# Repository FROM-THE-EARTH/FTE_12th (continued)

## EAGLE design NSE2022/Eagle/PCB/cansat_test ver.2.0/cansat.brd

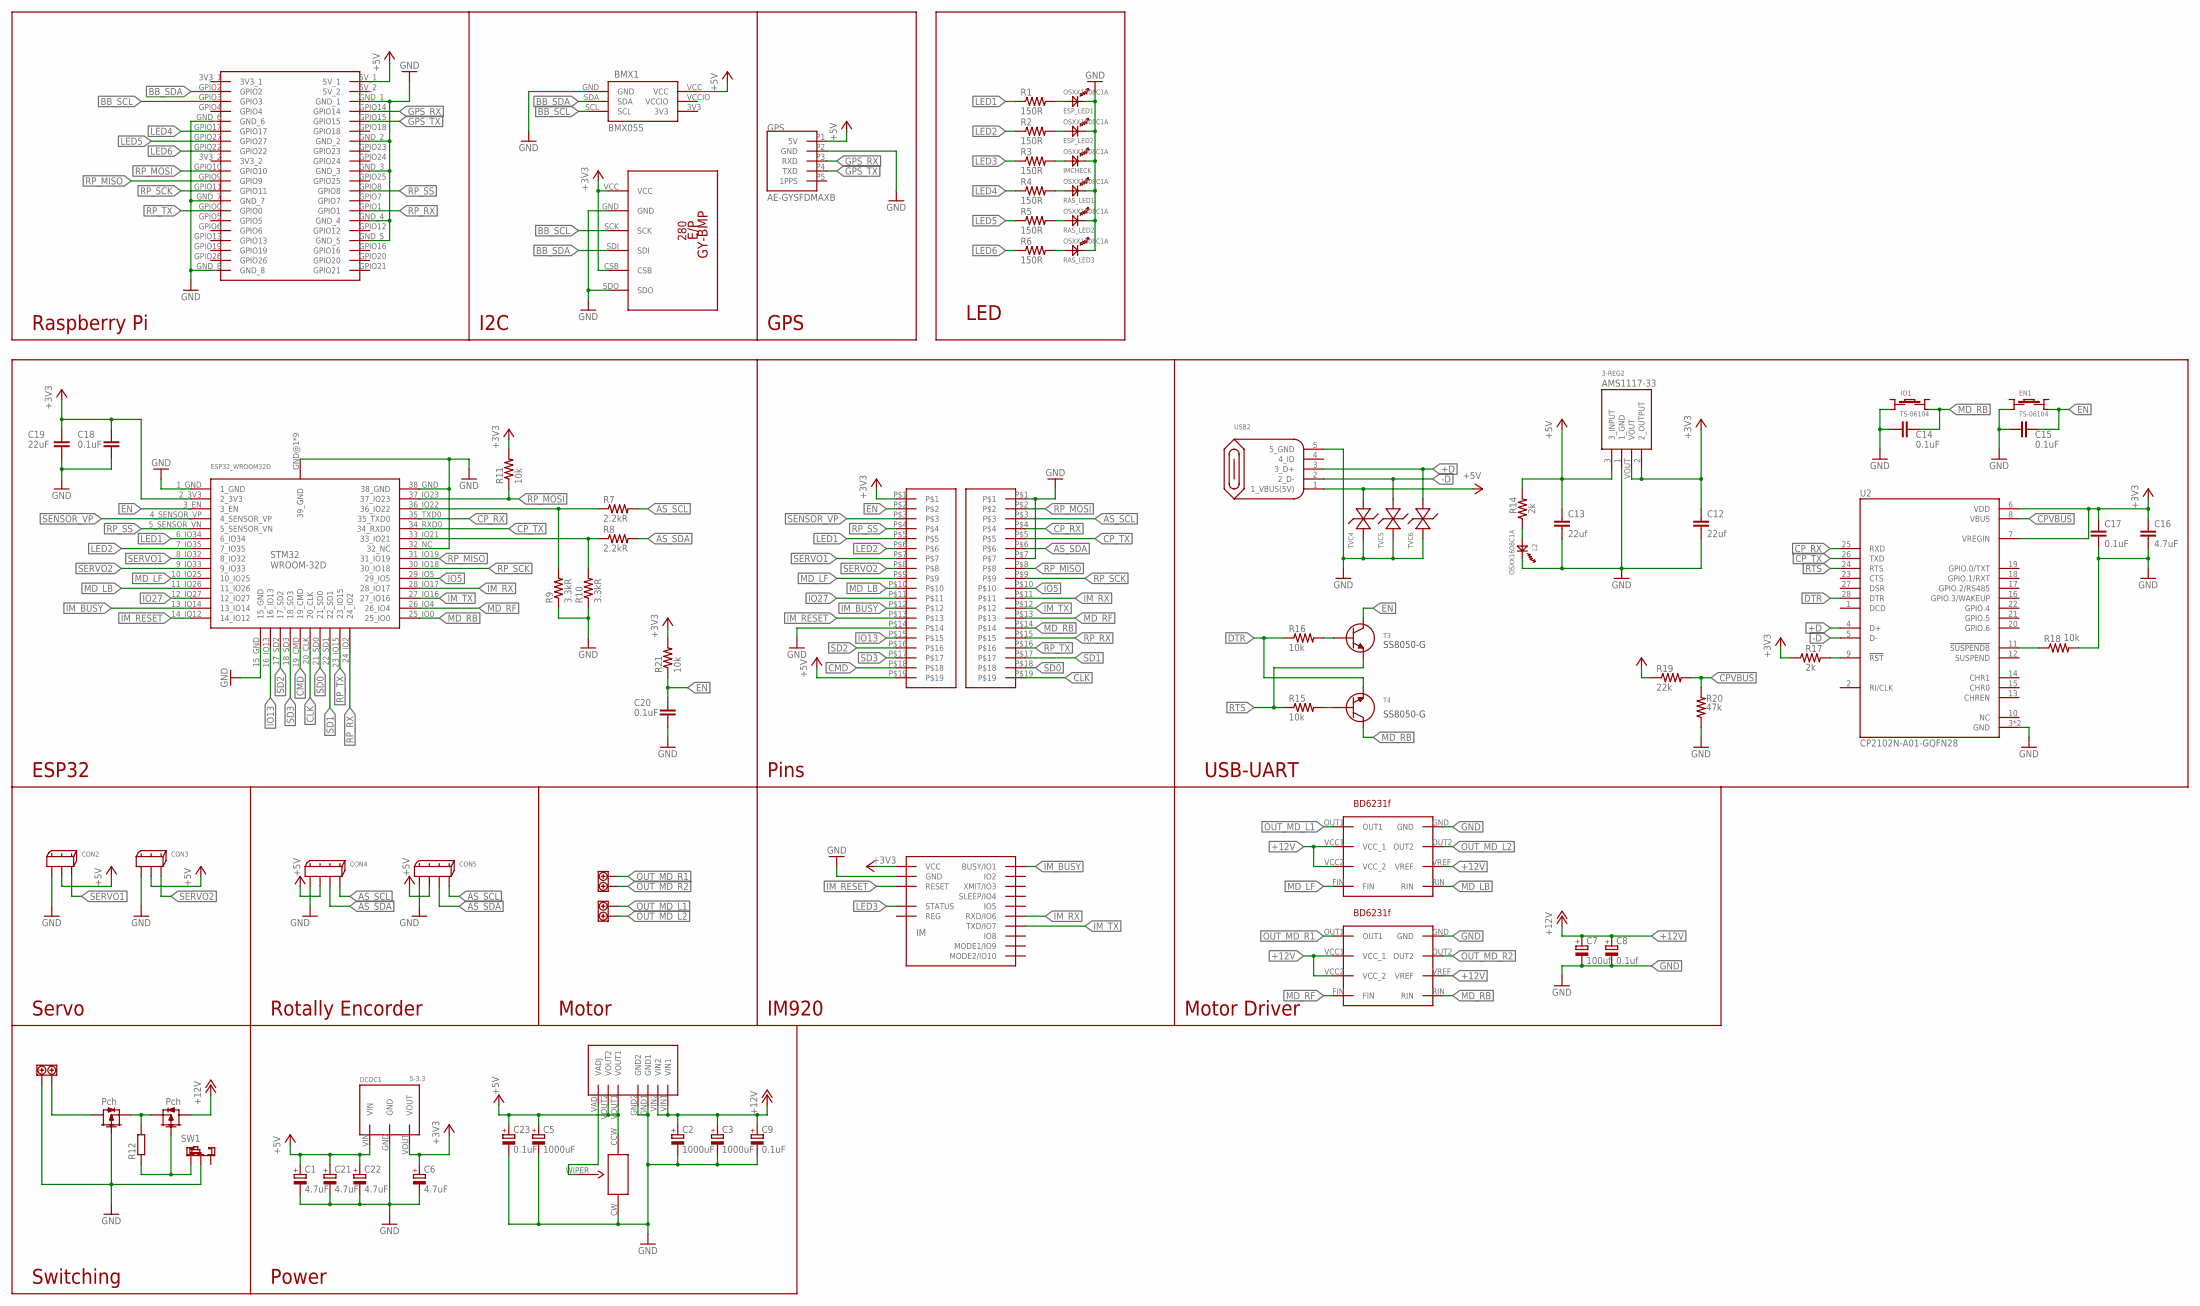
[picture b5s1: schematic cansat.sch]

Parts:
3-REG2: AZ1117CH-3.3TRG1
100KR1: 100kR; 3362P
BMX1: BMX055
C1, C6, C21, C22: 4.7uF; E2,5-7
C2, C3, C5: 1000uF; E5-10,5
C7: 100uf; E2,5-7
C8: 0.1uf; E2,5-7
C9: 0.1uF; E2,5-7
C12, C13: 22uf; C0603
C14, C15, C17, C18, C20: 0.1uF; C0603
C16: 4.7uF; C0402
C19: 22uF; C0603
C23: 0.1uF; E5-10,5
CON2, CON3: 2.5_MINI-SPOX_3PIN
CON4, CON5: 2.5_MINI-SPOX_4PIN
DCDC1: 5-3.3; 3.3V0.5A_M78AR05-0.5
EN1: TS-06104
ESP32_WROOM32D: ESP32-WROOM-32D
ESP_LED1, ESP_LED2: OSXX1608C1A
GPS: AE-GYSFDMAXB
IM: IM920C
IMCHECK: OSXX1608C1A
IO1: TS-06104
L2: OSXX1608C1A
MD_L: BD6231F
MD_R: BD6231F
PIN_L: 19_2.54
PIN_R: 19_2.54
R1, R2, R3, R4, R5, R6: 150R; R0603
R7, R8: 2.2kR; R0603
R9, R10: 3.3kR; R0603
R11, R15, R16, R18, R21: 10k; R0201
R12: R-EU_0207/10; 0207/10
R14, R17: 2k; R0201
R19: 22k; R0201
R20: 47k; R0201
RASPBERRYPI_4B: RASPBERRYPI4B
RAS_LED1, RAS_LED2, RAS_LED3: OSXX1608C1A
SW1: SRIDE_SWITCH
T3, T4: NPN_SS8050-G
TM1, TM2, TM3: TERMINAL_SLOPED_2PIN
TVC4, TVC5, TVC6: ESD5484FCT5G
U2: CP2102N-A01-GQFN28; QFN50P500X500X80-29N
U$7, U$10: 2SJ681-PCH; 2SJ681
U$8: 5V3A_KIC-053
U$9: GY-BPM280; GY-BMP280-FOOTPRINT
USB2: MICRO-B_ZX62R-B-5P

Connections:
3V3: BMX1.3V3
+3V3: 3-REG2.2 (2_OUTPUT), 3-REG2.VOUT, C6.+, C12.1, C16.1, C17.1, C18.1, C19.1, DCDC1.VOUT, ESP32_WROOM32D.2_3V3, IM.$P17 (VCC), PIN_L.P$1, R11.2, R17.1, R21.2, U2.6 (VDD), U2.7 (VREGIN), U$9.CSB, U$9.VCC
+12V: C2.+, C3.+, C7.+, C8.+, C9.+, MD_L.VCC1 (VCC_1), MD_L.VCC2 (VCC_2), MD_L.VREF, MD_R.VCC1 (VCC_1), MD_R.VCC2 (VCC_2), MD_R.VREF, U$8.VIN1, U$8.VIN2, U$10.DRAIN
+D: TVC6.2_AN, U2.4 (D+), USB2.3 (3_D+)
-D: TVC5.2_AN, U2.5 (D-), USB2.2 (2_D-)
A7_1: R12.2, U$7.SOURCE, U$10.SOURCE
AS_SCL: CON4.P$4 (4), CON5.P$4 (4), PIN_R.P$3, R7.2
AS_SDA: CON4.P$3 (3), CON5.P$3 (3), PIN_R.P$6, R8.2
BB_SCL: BMX1.SCL, RASPBERRYPI_4B.GPIO3, U$9.SCK
BB_SDA: BMX1.SDA, RASPBERRYPI_4B.GPIO2, U$9.SDI
CLK: ESP32_WROOM32D.20_CLK, PIN_R.P$19
CMD: ESP32_WROOM32D.19_CMD, PIN_L.P$18
CPVBUS: R19.2, R20.2, U2.8 (VBUS)
CP_RX: ESP32_WROOM32D.35_TXD0, PIN_R.P$4, U2.25 (RXD)
CP_TX: ESP32_WROOM32D.34_RXD0, PIN_R.P$5, U2.26 (TXD)
DTR: R16.1, T4.2, U2.28 (DTR)
EN: C15.1, C20.1, EN1.D, ESP32_WROOM32D.3_EN, PIN_L.P$2, R21.1, T3.3
GPS_RX: GPS.P3 (RXD), RASPBERRYPI_4B.GPIO14
GPS_TX: GPS.P4 (TXD), RASPBERRYPI_4B.GPIO15
IM_BUSY: ESP32_WROOM32D.13_IO14, IM.$P1 (BUSY/IO1), PIN_L.P$12
IM_RESET: ESP32_WROOM32D.14_IO12, IM.$P19 (RESET), PIN_L.P$13
IM_RX: ESP32_WROOM32D.28_IO17, IM.$P6 (RXD/IO6), PIN_R.P$11
IM_TX: ESP32_WROOM32D.27_IO16, IM.$P7 (TXD/IO7), PIN_R.P$12
IO5: ESP32_WROOM32D.29_IO5, PIN_R.P$10
IO13: ESP32_WROOM32D.16_IO13, PIN_L.P$15
IO27: ESP32_WROOM32D.12_IO27, PIN_L.P$11
LED1: ESP32_WROOM32D.6_IO34, PIN_L.P$5, R1.1
LED2: ESP32_WROOM32D.7_IO35, PIN_L.P$6, R2.1
LED3: IM.$P15 (STATUS), R3.1
LED4: R4.1, RASPBERRYPI_4B.GPIO17
LED5: R5.1, RASPBERRYPI_4B.GPIO27
LED6: R6.1, RASPBERRYPI_4B.GPIO22
MD_LB: ESP32_WROOM32D.11_IO26, MD_L.RIN, PIN_L.P$10
MD_LF: ESP32_WROOM32D.10_IO25, MD_L.FIN, PIN_L.P$9
MD_RB: C14.1, ESP32_WROOM32D.25_IO0, IO1.D, MD_R.RIN, PIN_R.P$14, T4.3
MD_RF: ESP32_WROOM32D.26_IO4, MD_R.FIN, PIN_R.P$13
unnamed: ESP_LED1.AN, R1.2
unnamed: ESP_LED2.AN, R2.2
unnamed: IMCHECK.AN, R3.2
unnamed: R4.2, RAS_LED1.AN
unnamed: R5.2, RAS_LED2.AN
unnamed: R6.2, RAS_LED3.AN
unnamed: ESP32_WROOM32D.36_IO22, R7.1, R9.2
unnamed: ESP32_WROOM32D.33_IO21, R8.1, R10.2
unnamed: TM3.1, U$7.DRAIN
unnamed: L2.AN, R14.1
unnamed: R16.2, T3.1
unnamed: R15.2, T4.1
unnamed: R17.2, U2.9 (!RST)
unnamed: R18.1, U2.11 (!SUSPENDB)
unnamed: 100KR1.WIPER, U$8.VADJ
unnamed: R12.1, SW1.L, U$10.GATE
OUT_MD_L1: MD_L.OUT1, TM2.1
OUT_MD_L2: MD_L.OUT2, TM2.2
OUT_MD_R1: MD_R.OUT1, TM1.1
OUT_MD_R2: MD_R.OUT2, TM1.2
RP_MISO: ESP32_WROOM32D.31_IO19, PIN_R.P$8, RASPBERRYPI_4B.GPIO9
RP_MOSI: ESP32_WROOM32D.37_IO23, PIN_R.P$2, R11.1, RASPBERRYPI_4B.GPIO10
RP_RX: ESP32_WROOM32D.24_IO2, PIN_R.P$15, RASPBERRYPI_4B.GPIO1
RP_SCK: ESP32_WROOM32D.30_IO18, PIN_R.P$9, RASPBERRYPI_4B.GPIO11
RP_SS: ESP32_WROOM32D.5_SENSOR_VN, PIN_L.P$4, RASPBERRYPI_4B.GPIO8
RP_TX: ESP32_WROOM32D.23_IO15, PIN_R.P$16, RASPBERRYPI_4B.GPIO0
RTS: R15.1, T3.2, U2.24 (RTS)
SD0: ESP32_WROOM32D.21_SD0, PIN_R.P$18
SD1: ESP32_WROOM32D.22_SD1, PIN_R.P$17
SD2: ESP32_WROOM32D.17_SD2, PIN_L.P$16
SD3: ESP32_WROOM32D.18_SD3, PIN_L.P$17
SENSOR_VP: ESP32_WROOM32D.4_SENSOR_VP, PIN_L.P$3
SERVO1: CON2.3, ESP32_WROOM32D.8_IO32, PIN_L.P$7
SERVO2: CON3.3, ESP32_WROOM32D.9_IO33, PIN_L.P$8
VCCIO: BMX1.VCCIO

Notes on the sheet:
SS8050-G
ESP32
Servo
Rotally Encorder
Motor
IM920
USB-UART
Raspberry Pi
I2C
GPS
Pins
Motor Driver
Switching
Power
LED

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
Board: 2 copper layers, 80 parts (0 on the bottom side), 72 nets, no tracks yet.
